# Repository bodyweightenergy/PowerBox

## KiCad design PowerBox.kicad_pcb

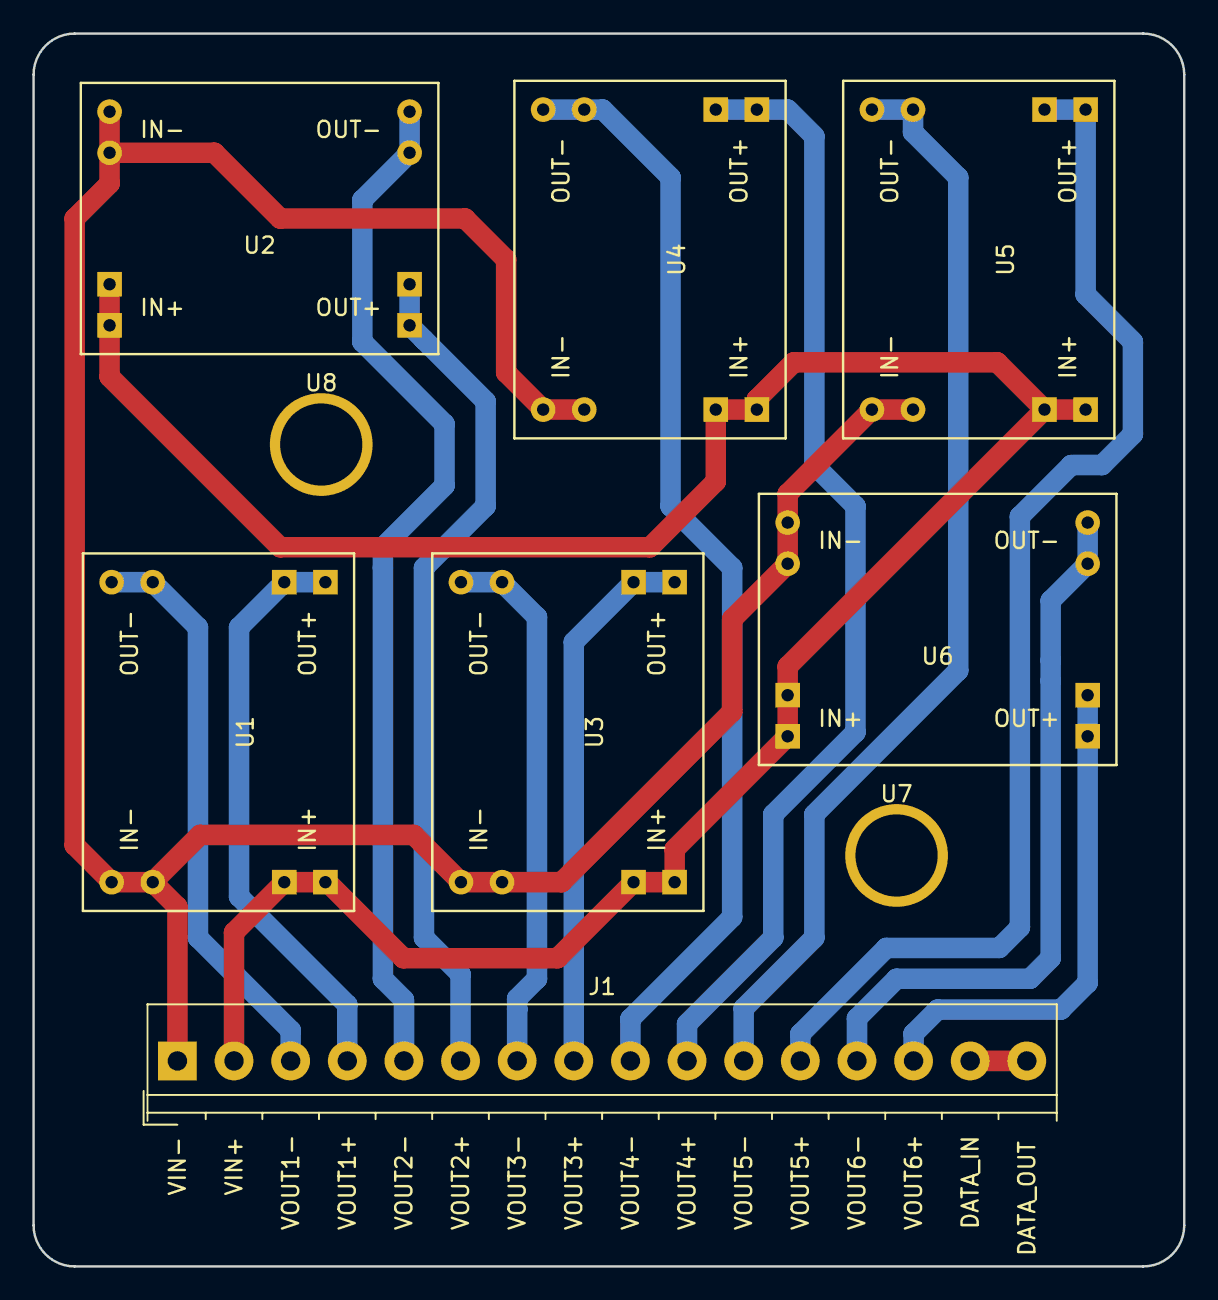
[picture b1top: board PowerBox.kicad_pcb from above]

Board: 2 copper layers, 71.1 x 76.2 mm, 9 parts (0 on the bottom side), 2 nets.

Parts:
J1: Screw_Terminal_01x16; TerminalBlock_4UCON_19963_16x3.5mm_Straight_MOD
U1, U2, U3, U4, U5, U6: MP1584EN
U7, U8: SCREW_HOLE; SCREW_HOLE_0.2in-dia

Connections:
unnamed: U1.1, U2.1, U3.1, U4.1, U5.1, U6.1
unnamed: U1.2, U2.2, U3.2, U4.2, U5.2, U6.2

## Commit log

2017-09-29 added PowerBox dimensional drawing
2017-09-29 added datasheets and material sourcing info
2017-09-29 renamed to be generic, added stackable pin/sockets
2017-09-30 initial PCB files commit
2017-09-30 fixed terminal block footprint. layed out tracks for all components.
2017-09-30 fixed MP1584EN footprint to have text
2017-09-30 generated GERBERs for EasyEDA test
2017-10-02 added rounded corners
2017-10-02 rerouted some tracks away from screw holes, with 25 mil grid.
2017-10-10 modified gerber settings & output directory
2017-10-10 removed drill map file (takes space on EasyEDA gerber viewer). regenerated gerbers to better work with EasyEDA.
2017-10-11 replaced screw holes with custom large through hole pads
